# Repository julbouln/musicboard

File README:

This project only use a CODEC, a QuadSPI NOR-flash and a STM32F7 microcontroller to provide a complete MIDI + audio USB soundcard.

Continuation of https://github.com/julbouln/stm32f7discovery_midi_synth prototype. It now uses a memory and computing optimized version of https://github.com/schellingb/TinySoundFont and includes STM32 cubemx source code. A dedicated custom board is also provided even though STM32F746 discovery board is supported by the firmware.

Features:
- Composite USB audio, USB MIDI and USB mass storage
- Integrated SF2 MIDI syntheziser
- Easy SF2 soundfont customization with USB mass storage
- Mixed MIDI synthesis and raw audio

Custom board with minimal requirements:
- STM32F746VET6 LQFP100 320kb ram + 512kb flash
- S25FL256S 32mb nor flash
- WM8731 codec

Update SF2 font (Linux):
When connected, Linux should show the Flash as mass storage:
sd 6:0:0:0: [sdb] 8192 4096-byte logical blocks: (33.6 MB/32.0 MiB)
sd 6:0:0:0: [sdb] Write Protect is off
sd 6:0:0:0: [sdb] Mode Sense: 22 00 00 00
sd 6:0:0:0: [sdb] Write cache: disabled, read cache: enabled, doesn't support DPO or FUA
sd 6:0:0:0: [sdb] Attached SCSI removable disk
You just need to dd the sf2 file to the disk (can take several minutes):
# dd if=yourfont.sf2 of=/dev/sdb bs=4096

Update SF2 font (balena Etcher)
You can also update the SF2 using balena Etcher https://www.balena.io/etcher/. This program is intended for OS image, but you can use it for SF2:
- you will need to rename your extension from .sf2 to .bin so Etcher can accept the file
- Etcher will warn you that the image is not an OS, just hit continue and select SF2 ROM drive

LED should blink if the font is properly recognized.

Notes:
Firmware tested with arm-none-eabi-gcc 9.2.1 20191025
SF2 fonts tested:
- TimGM6mb http://www.timbrechbill.com/saxguru/Timidity.php
- GeneralUser GS http://www.schristiancollins.com/generaluser.php (custom board only, 32mb font)
Default make for STM32F746-DISCO board, use "make BOARD=MUSICBOARD" for custom board firmware.

TODO:
- bug: synthesis sometimes make a "click" noise
- feature: TinySoundFont does not fully implement SF2 (modulators)
- feature: Add MIDI IN/OUT uart interfaces
- feature: USB-MIDI to MIDI interface (add MIDI-IN and MIDI-OUT)
- feature: Audio IN
- feature: Add sysex for chorus & reverb control

Sources:
- https://github.com/STMicroelectronics/STM32CubeF7

SF2:
- https://github.com/schellingb/TinySoundFont

USB audio with asynchronous feedback
- https://github.com/dragonman225/stm32f469-usbaudio
- https://github.com/ada-sound/X-CUBE-USB-AUDIO
- https://github.com/Lefucjusz/Lefucjusz-USB-DAC

USB composite:
- https://github.com/sanuch14/STM32_CompositeHID_CDC

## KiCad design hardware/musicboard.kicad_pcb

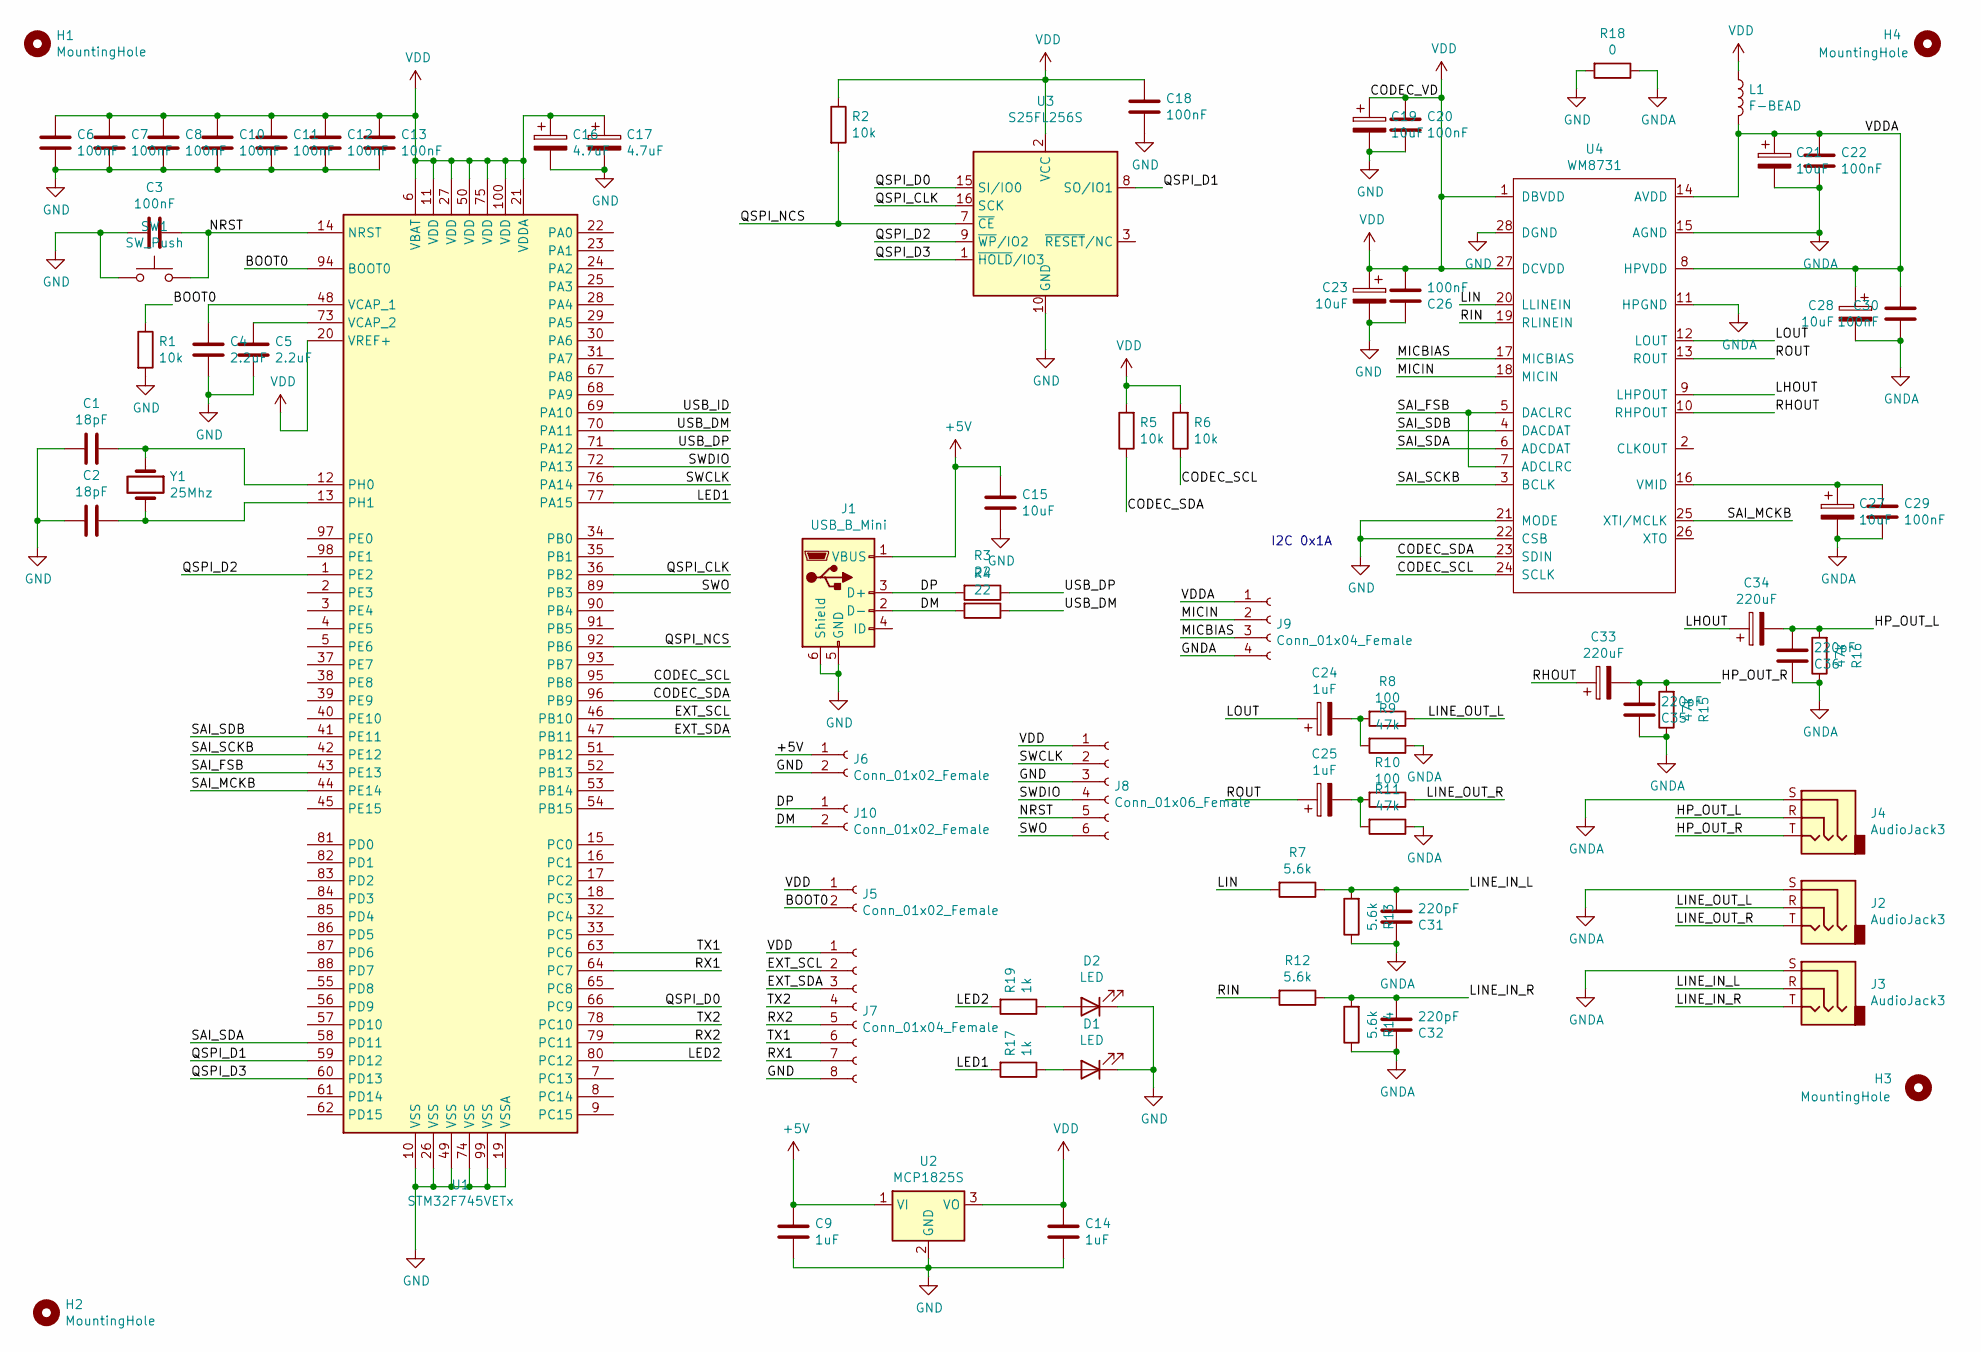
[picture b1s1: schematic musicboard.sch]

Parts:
C1, C2: 18pF; C_0603_1608Metric_Pad1.05x0.95mm_HandSolder
C3, C6, C7, C8, C10, C11, C12, C13, C18, C20, C22, C26, C29, C30: 100nF; C_0603_1608Metric_Pad1.05x0.95mm_HandSolder
C4, C5: 2.2uF; C_0603_1608Metric_Pad1.05x0.95mm_HandSolder
C9, C14: 1uF; C_0603_1608Metric_Pad1.05x0.95mm_HandSolder
C15, C19, C21, C23, C27, C28: 10uF; C_0805_2012Metric_Pad1.15x1.40mm_HandSolder
C16, C17: 4.7uF; C_0805_2012Metric_Pad1.15x1.40mm_HandSolder
C24, C25: 1uF; C_Elec_4x5.4
C31, C32, C35, C36: 220pF; C_0603_1608Metric_Pad1.05x0.95mm_HandSolder
C33, C34: 220uF; C_Elec_6.3x5.4
D1, D2: LED; LED_0603_1608Metric_Pad1.05x0.95mm_HandSolder
H1, H2, H3, H4: MountingHole; MountingHole_2.7mm_M2.5
J1: USB_B_Mini; USB-mini-B-0548190519
J2, J3, J4: AudioJack3; Jack_3.5mm_CUI_SJ1-3535NG_Horizontal
J5, J6, J10: Conn_01x02_Female; PinHeader_1x02_P2.54mm_Vertical
J7: Conn_01x04_Female; PinHeader_1x08_P2.54mm_Vertical
J8: Conn_01x06_Female; PinHeader_1x06_P2.54mm_Vertical
J9: Conn_01x04_Female; PinHeader_1x04_P2.54mm_Vertical
L1: F-BEAD; L_0805_2012Metric_Pad1.15x1.40mm_HandSolder
R1, R2, R5, R6: 10k; R_0603_1608Metric_Pad1.05x0.95mm_HandSolder
R3, R4: 22; R_0603_1608Metric_Pad1.05x0.95mm_HandSolder
R7, R12, R13, R14: 5.6k; R_0603_1608Metric_Pad1.05x0.95mm_HandSolder
R8, R10: 100; R_0603_1608Metric_Pad1.05x0.95mm_HandSolder
R9, R11, R15, R16: 47k; R_0603_1608Metric_Pad1.05x0.95mm_HandSolder
R17, R19: 1k; R_0603_1608Metric_Pad1.05x0.95mm_HandSolder
R18: 0; R_0805_2012Metric_Pad1.15x1.40mm_HandSolder
SW1: SW_Push; SW_SPST_B3U-3000P
U1: STM32F745VETx; LQFP-100_14x14mm_P0.5mm
U2: MCP1825S; SOT-223-3_TabPin2
U3: S25FL256S; SOIC-16W_7.5x10.3mm_P1.27mm
U4: WM8731; SSOP-28_5.3x10.2mm_P0.65mm
Y1: 25Mhz; Crystal_SMD_5032-2Pin_5.0x3.2mm_HandSoldering

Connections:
+5V: C9.1, C15.1, J1.1 (VBUS), J6.1, U2.1 (VI)
/BOOT0: J5.2, R1.1, U1.94 (BOOT0)
/CODEC_SCL: R6.1, U1.95 (PB8), U4.24 (SCLK)
/CODEC_SDA: R5.1, U1.96 (PB9), U4.23 (SDIN)
/DM: J1.2 (D-), J10.2, R4.2
/DP: J1.3 (D+), J10.1, R3.2
/EXT_SCL: J7.2, U1.46 (PB10)
/EXT_SDA: J7.3, U1.47 (PB11)
/HP_OUT_L: C34.2, C36.2, J4.R, R16.2
/HP_OUT_R: C33.2, C35.2, J4.T, R15.2
/LED1: R17.2, U1.77 (PA15)
/LED2: R19.2, U1.80 (PC12)
/LHOUT: C34.1, U4.9 (LHPOUT)
/LIN: R7.2, U4.20 (LLINEIN)
/LINE_IN_L: C31.2, J3.R, R7.1, R13.2
/LINE_IN_R: C32.2, J3.T, R12.1, R14.2
/LINE_OUT_L: J2.R, R8.1
/LINE_OUT_R: J2.T, R10.1
/LOUT: C24.1, U4.12 (LOUT)
/MICBIAS: J9.3, U4.17 (MICBIAS)
/MICIN: J9.2, U4.18 (MICIN)
/NRST: C3.1, J8.5, SW1.2, U1.14 (NRST)
/QSPI_CLK: U1.36 (PB2), U3.16 (SCK)
/QSPI_D0: U1.66 (PC9), U3.15 (SI/IO0)
/QSPI_D1: U1.59 (PD12), U3.8 (SO/IO1)
/QSPI_D2: U1.1 (PE2), U3.9 (~WP~/IO2)
/QSPI_D3: U1.60 (PD13), U3.1 (~HOLD~/IO3)
/QSPI_NCS: R2.2, U1.92 (PB6), U3.7 (~CE)
/RHOUT: C33.1, U4.10 (RHPOUT)
/RIN: R12.2, U4.19 (RLINEIN)
/ROUT: C25.1, U4.13 (ROUT)
/RX1: J7.7, U1.64 (PC7)
/RX2: J7.5, U1.79 (PC11)
/SAI_FSB: U1.43 (PE13), U4.5 (DACLRC), U4.7 (ADCLRC)
/SAI_MCKB: U1.44 (PE14), U4.25 (XTI/MCLK)
/SAI_SCKB: U1.42 (PE12), U4.3 (BCLK)
/SAI_SDA: U1.58 (PD11), U4.6 (ADCDAT)
/SAI_SDB: U1.41 (PE11), U4.4 (DACDAT)
/SWCLK: J8.2, U1.76 (PA14)
/SWDIO: J8.4, U1.72 (PA13)
/SWO: J8.6, U1.89 (PB3)
/TX1: J7.6, U1.63 (PC6)
/TX2: J7.4, U1.78 (PC10)
/USB_DM: R4.1, U1.70 (PA11)
/USB_DP: R3.1, U1.71 (PA12)
/USB_ID: U1.69 (PA10)
/VDDA: C21.1, C22.1, C28.1, C30.1, J9.1, L1.2, U4.8 (HPVDD), U4.14 (AVDD)
GND: C1.2, C2.2, C3.2, C4.2, C5.2, C6.2, C7.2, C8.2, C9.2, C10.2, C11.2, C12.2, C13.2, C14.2, C15.2, C16.2, C17.2, C18.2, C19.2, C20.2, C23.2, C26.1, D1.1 (K), D2.1 (K), J1.5 (GND), J1.6 (Shield), J6.2, J7.8, J8.3, R1.2, R18.2, SW1.1, U1.10 (VSS), U1.19 (VSSA), U1.26 (VSS), U1.49 (VSS), U1.74 (VSS), U1.99 (VSS), U2.2 (GND), U3.10 (GND), U4.21 (MODE), U4.22 (CSB), U4.28 (DGND)
GNDA: C21.2, C22.2, C27.2, C28.2, C29.2, C30.2, C31.1, C32.1, C35.1, C36.1, J2.S, J3.S, J4.S, J9.4, R9.1, R11.1, R13.1, R14.1, R15.1, R16.1, R18.1, U4.11 (HPGND), U4.15 (AGND)
unnamed: C1.1, U1.12 (PH0), Y1.1
unnamed: C2.1, U1.13 (PH1), Y1.2
unnamed: C4.1, U1.48 (VCAP_1)
unnamed: C5.1, U1.73 (VCAP_2)
unnamed: C24.2, R8.2, R9.2
unnamed: C25.2, R10.2, R11.2
unnamed: C27.1, C29.1, U4.16 (VMID)
unnamed: D1.2 (A), R17.1
unnamed: D2.2 (A), R19.1
VDD: C6.1, C7.1, C8.1, C10.1, C11.1, C12.1, C13.1, C14.1, C16.1, C17.1, C18.1, C19.1, C20.1, C23.1, C26.2, J5.1, J7.1, J8.1, L1.1, R2.1, R5.2, R6.2, U1.6 (VBAT), U1.11 (VDD), U1.20 (VREF+), U1.21 (VDDA), U1.27 (VDD), U1.50 (VDD), U1.75 (VDD), U1.100 (VDD), U2.3 (VO), U3.2 (VCC), U4.1 (DBVDD), U4.27 (DCVDD)

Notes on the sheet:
I2C 0x1A

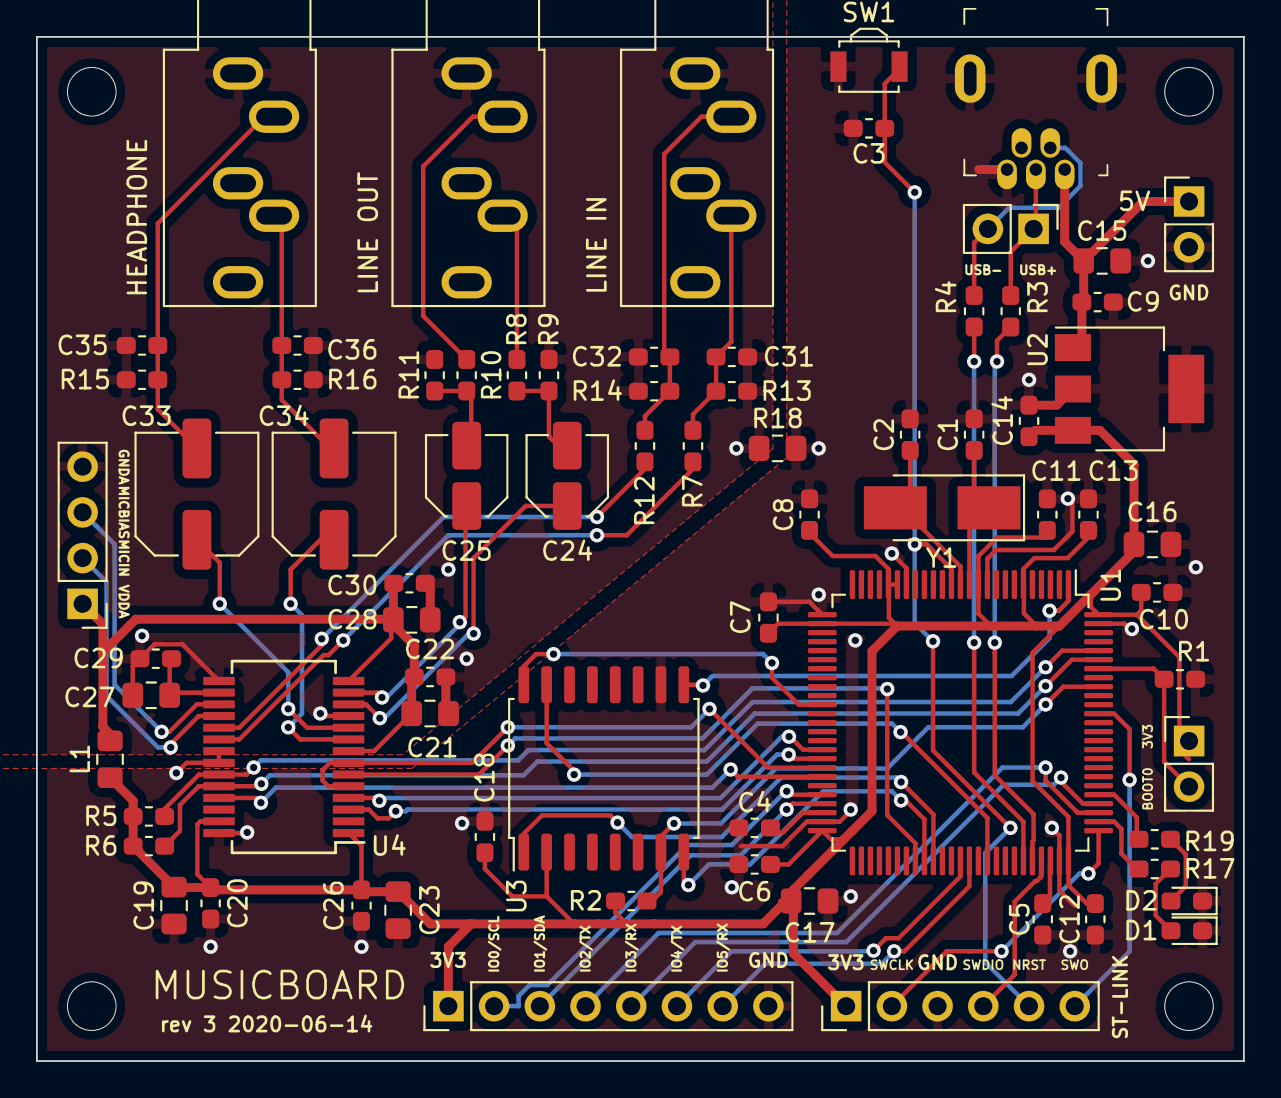
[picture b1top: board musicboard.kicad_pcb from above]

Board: 2 copper layers, 67.1 x 56.9 mm, 78 parts (0 on the bottom side), 58 nets.

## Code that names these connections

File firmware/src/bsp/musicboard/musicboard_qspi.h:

/**
  ******************************************************************************
  * @file    stm32746g_discovery_qspi.h
  * @author  MCD Application Team
  * @brief   This file contains the common defines and functions prototypes for
  *          the stm32746g_discovery_qspi.c driver.
  ******************************************************************************
  * @attention
  *
  * <h2><center>&copy; COPYRIGHT(c) 2016 STMicroelectronics</center></h2>
  *
  * Redistribution and use in source and binary forms, with or without modification,
  * are permitted provided that the following conditions are met:
  *   1. Redistributions of source code must retain the above copyright notice,
  *      this list of conditions and the following disclaimer.
  *   2. Redistributions in binary form must reproduce the above copyright notice,
  *      this list of conditions and the following disclaimer in the documentation
  *      and/or other materials provided with the distribution.
  *   3. Neither the name of STMicroelectronics nor the names of its contributors
  *      may be used to endorse or promote products derived from this software
  *      without specific prior written permission.
  *
  * THIS SOFTWARE IS PROVIDED BY THE COPYRIGHT HOLDERS AND CONTRIBUTORS "AS IS"
  * AND ANY EXPRESS OR IMPLIED WARRANTIES, INCLUDING, BUT NOT LIMITED TO, THE
  * IMPLIED WARRANTIES OF MERCHANTABILITY AND FITNESS FOR A PARTICULAR PURPOSE ARE
  * DISCLAIMED. IN NO EVENT SHALL THE COPYRIGHT HOLDER OR CONTRIBUTORS BE LIABLE
  * FOR ANY DIRECT, INDIRECT, INCIDENTAL, SPECIAL, EXEMPLARY, OR CONSEQUENTIAL
  * DAMAGES (INCLUDING, BUT NOT LIMITED TO, PROCUREMENT OF SUBSTITUTE GOODS OR
  * SERVICES; LOSS OF USE, DATA, OR PROFITS; OR BUSINESS INTERRUPTION) HOWEVER
  * CAUSED AND ON ANY THEORY OF LIABILITY, WHETHER IN CONTRACT, STRICT LIABILITY,
  * OR TORT (INCLUDING NEGLIGENCE OR OTHERWISE) ARISING IN ANY WAY OUT OF THE USE
  * OF THIS SOFTWARE, EVEN IF ADVISED OF THE POSSIBILITY OF SUCH DAMAGE.
  *
  ******************************************************************************
  */ 

/** @addtogroup BSP
  * @{
  */ 

/** @addtogroup STM32746G_DISCOVERY
  * @{
  */
    
/* Define to prevent recursive inclusion -------------------------------------*/
#ifndef __MUSICBOARD_QSPI_H
#define __MUSICBOARD_QSPI_H

#ifdef __cplusplus
 extern "C" {
#endif 

/* Includes ------------------------------------------------------------------*/
#include "stm32f7xx_hal.h"
#include "s25fl256.h"

/** @addtogroup STM32746G_DISCOVERY_QSPI
  * @{
  */    

  
/* Exported constants --------------------------------------------------------*/ 
/** @defgroup STM32746G_DISCOVERY_QSPI_Exported_Constants STM32746G_DISCOVERY_QSPI Exported Constants
  * @{
  */
/* QSPI Error codes */
#define QSPI_OK            ((uint8_t)0x00)
#define QSPI_ERROR         ((uint8_t)0x01)
#define QSPI_BUSY          ((uint8_t)0x02)
#define QSPI_NOT_SUPPORTED ((uint8_t)0x04)
#define QSPI_SUSPENDED     ((uint8_t)0x08)


/* Definition for QSPI clock resources */
#define QSPI_CLK_ENABLE()          __HAL_RCC_QSPI_CLK_ENABLE()
#define QSPI_CLK_DISABLE()         __HAL_RCC_QSPI_CLK_DISABLE()
#define QSPI_CS_GPIO_CLK_ENABLE()  __HAL_RCC_GPIOB_CLK_ENABLE()
#define QSPI_CLK_GPIO_CLK_ENABLE() __HAL_RCC_GPIOB_CLK_ENABLE()
#define QSPI_D0_GPIO_CLK_ENABLE()  __HAL_RCC_GPIOC_CLK_ENABLE()
#define QSPI_D1_GPIO_CLK_ENABLE()  __HAL_RCC_GPIOD_CLK_ENABLE()
#define QSPI_D2_GPIO_CLK_ENABLE()  __HAL_RCC_GPIOE_CLK_ENABLE()
#define QSPI_D3_GPIO_CLK_ENABLE()  __HAL_RCC_GPIOD_CLK_ENABLE()

#define QSPI_FORCE_RESET()         __HAL_RCC_QSPI_FORCE_RESET()
#define QSPI_RELEASE_RESET()       __HAL_RCC_QSPI_RELEASE_RESET()

/* Definition for QSPI Pins */
#define QSPI_CS_PIN                GPIO_PIN_6
#define QSPI_CS_GPIO_PORT          GPIOB
#define QSPI_CLK_PIN               GPIO_PIN_2
#define QSPI_CLK_GPIO_PORT         GPIOB
#define QSPI_D0_PIN                GPIO_PIN_9
#define QSPI_D0_GPIO_PORT          GPIOC
#define QSPI_D1_PIN                GPIO_PIN_12
#define QSPI_D1_GPIO_PORT          GPIOD
#define QSPI_D2_PIN                GPIO_PIN_2
#define QSPI_D2_GPIO_PORT          GPIOE
#define QSPI_D3_PIN                GPIO_PIN_13
#define QSPI_D3_GPIO_PORT          GPIOD

/* S25FL256 memory */
/* Size of the flash */
#define QSPI_FLASH_SIZE            23     /* Address bus width to access whole memory space */
#define QSPI_PAGE_SIZE             256

/* This alias is added as the name of Memory mapped fucntion changed */   
#define BSP_QSPI_MemoryMappedMode  BSP_QSPI_EnableMemoryMappedMode   
/**
  * @}
  */

/* Exported types ------------------------------------------------------------*/
/** @defgroup STM32746G_DISCOVERY_QSPI_Exported_Types STM32746G_DISCOVERY_QSPI Exported Types
  * @{
  */
/* QSPI Info */
typedef struct {
  uint32_t FlashSize;          /*!< Size of the flash */
  uint32_t EraseSectorSize;    /*!< Size of sectors for the erase operation */
  uint32_t EraseSectorsNumber; /*!< Number of sectors for the erase operation */
  uint32_t ProgPageSize;       /*!< Size of pages for the program operation */
  uint32_t ProgPagesNumber;    /*!< Number of pages for the program operation */
} QSPI_Info;

/**
  * @}
  */

  
/* Exported functions --------------------------------------------------------*/
/** @addtogroup STM32746G_DISCOVERY_QSPI_Exported_Functions
  * @{
  */  
uint8_t BSP_QSPI_Init       (void);
uint8_t BSP_QSPI_DeInit     (void);
uint8_t BSP_QSPI_Read       (uint8_t* pData, uint32_t ReadAddr, uint32_t Size);
uint8_t BSP_QSPI_Write      (uint8_t* pData, uint32_t WriteAddr, uint32_t Size);
uint8_t BSP_QSPI_Erase_Block(uint32_t BlockAddress);
uint8_t BSP_QSPI_Erase_Chip (void);
uint8_t BSP_QSPI_GetStatus  (void);
uint8_t BSP_QSPI_GetInfo    (QSPI_Info* pInfo);
uint8_t BSP_QSPI_EnableMemoryMappedMode(void);

/* These functions can be modified in case the current settings
   need to be changed for specific application needs */
void BSP_QSPI_MspInit(QSPI_HandleTypeDef *hqspi, void *Params);
void BSP_QSPI_MspDeInit(QSPI_HandleTypeDef *hqspi, void *Params);

/**
  * @}
  */ 

/**
  * @}
  */ 

#ifdef __cplusplus
}
#endif

#endif /* __STM32746G_DISCOVERY_QSPI_H */
/**
  * @}
  */ 

/**
  * @}
  */ 

/************************ (C) COPYRIGHT STMicroelectronics *****END OF FILE****/

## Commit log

2020-06-11 add pdf schematics
2020-06-12 add extension to board + add former fluidsynth
2020-06-14 use usb mini b + add usb header
2020-06-14 update schematics
2020-06-14 add vdda
2020-06-15 realign label
2020-06-16 misc
2020-06-19 add missing file
2020-06-24 add reverb
2020-06-25 add chorus
2020-06-25 quiet
2020-06-26 add synth program
2020-06-26 proper GM2 chorus and reverb support
2020-06-26 cleanup
2020-06-27 working chorus and reverb but only for 48 voices
2020-06-28 optimization & refactoring
2020-06-29 optimizations to support 64 voices with chorus & reverb
2020-07-01 add sysex support
2020-07-04 add usb midi sysex support
2020-07-04 quiet unsupported
2020-07-14 fix audio async feedback + improve sysex support
2020-07-15 refactoring
2020-07-19 WIP use freertos
2020-07-19 WIP freertos fix
2020-07-19 WIP freertos stack
2020-07-20 WIP freertos
